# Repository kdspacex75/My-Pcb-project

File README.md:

# PCB Night-Vision Robot 🤖🔦

Custom Arduino UNO-compatible PCB design and robot prototype for obstacle detection with night vision.

## Features
- Designed PCB using **KiCad** and 3D modeled in **Fusion 360**
- Integrated night-vision sensors for obstacle detection
- Fully assembled robot hardware with Arduino-based control
- Hands-on electronics + robotics integration

## Tech Stack
- KiCad (PCB Design)
- Autodesk Fusion 360
- Arduino (C/C++)

---

### 🔗 Repository Info
This project was part of my robotics learning and showcases PCB design + embedded system integration.

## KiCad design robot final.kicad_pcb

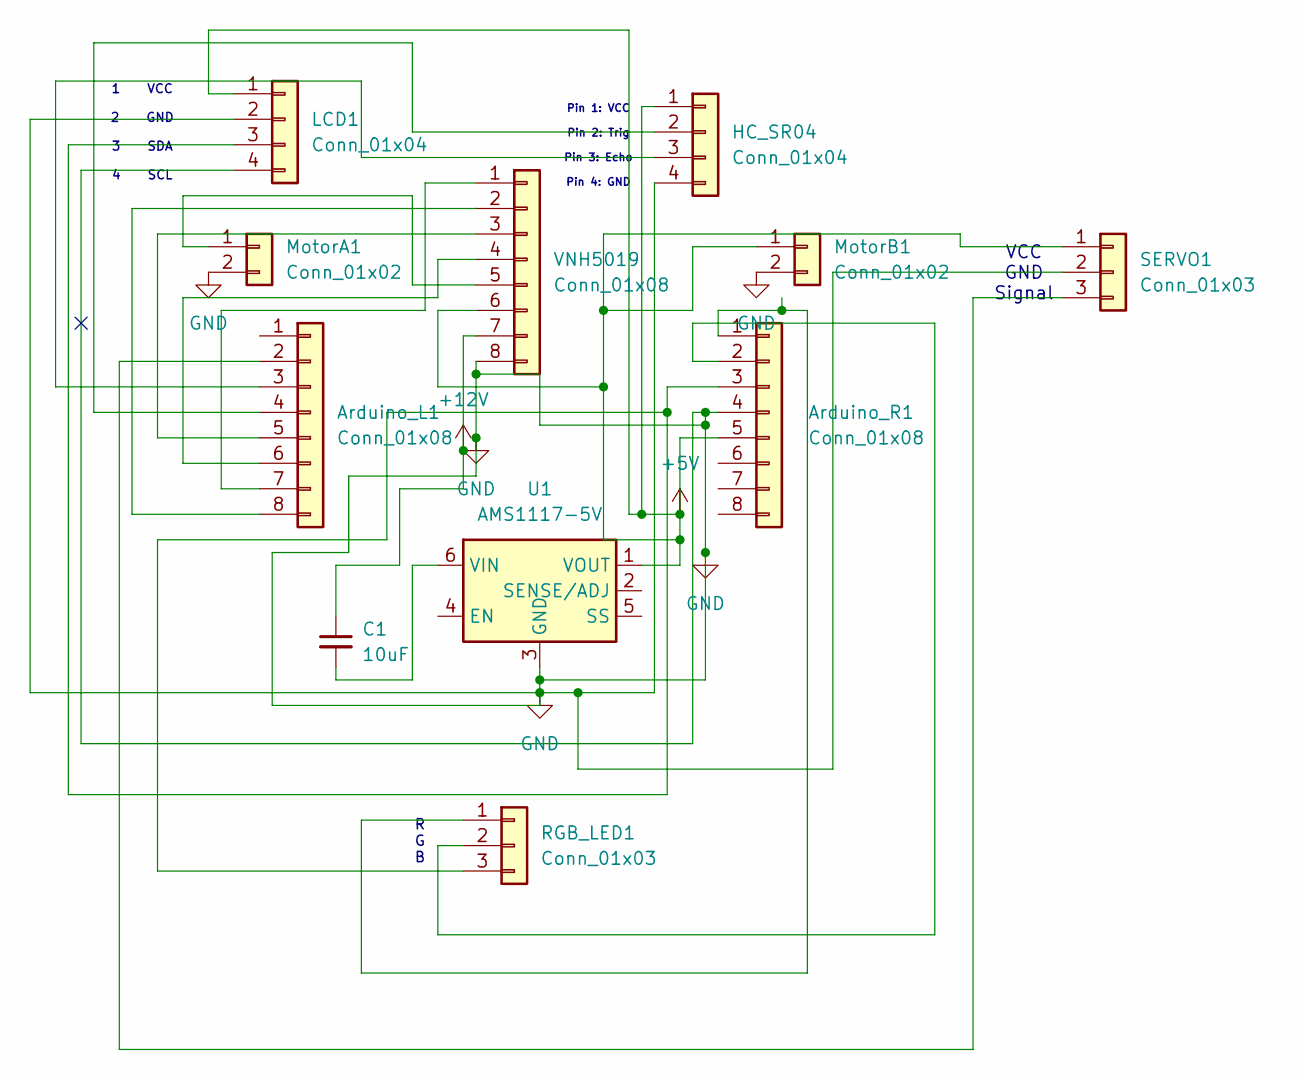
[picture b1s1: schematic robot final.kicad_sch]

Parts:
Arduino_L1: Conn_01x08; PinHeader_1x08_P2.54mm_Vertical
Arduino_R1: Conn_01x08; PinHeader_1x08_P2.54mm_Vertical
C1: 10uF; PinHeader_1x08_P2.54mm_Vertical
HC_SR04: Conn_01x04; PinHeader_1x04_P2.54mm_Vertical
LCD1: Conn_01x04; PinHeader_1x04_P2.54mm_Vertical
MotorA1: Conn_01x02; PinHeader_1x02_P2.54mm_Vertical
MotorB1: Conn_01x02; PinHeader_1x02_P2.54mm_Vertical
RGB_LED1: Conn_01x03; PinHeader_1x03_P2.54mm_Vertical
SERVO1: Conn_01x03; PinHeader_1x03_P2.54mm_Vertical
U1: AMS1117-5V; LFCSP-6-1EP_2x2mm_P0.65mm_EP1x1.6mm
VNH5019: Conn_01x08; PinHeader_1x08_P2.54mm_Vertical

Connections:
+5V: Arduino_R1.5, HC_SR04.1, LCD1.1, MotorB1.1, SERVO1.1, U1.1 (VOUT), VNH5019.6
+12V: C1.1, VNH5019.7
GND: Arduino_R1.4, HC_SR04.4, LCD1.2, LCD1.4, MotorA1.2, MotorB1.2, SERVO1.2, U1.3 (GND), U1.7 (GND), VNH5019.8
unnamed: Arduino_L1.2, SERVO1.3
unnamed: Arduino_L1.3, HC_SR04.3
unnamed: Arduino_L1.4, HC_SR04.2
unnamed: Arduino_L1.5, VNH5019.3
unnamed: Arduino_L1.6, VNH5019.4
unnamed: Arduino_L1.7, VNH5019.1
unnamed: Arduino_L1.8, VNH5019.2
unnamed: Arduino_R1.1, RGB_LED1.1
unnamed: Arduino_R1.2, RGB_LED1.2
unnamed: Arduino_R1.3, LCD1.3, RGB_LED1.3
unnamed: MotorA1.1, VNH5019.5
unnamed: C1.2, U1.6 (VIN)

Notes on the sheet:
VCC GND Signal
1 VCC 2 GND 3 SDA 4 SCL
R G B
Pin 1: VCC Pin 2: Trig Pin 3: Echo Pin 4: GND

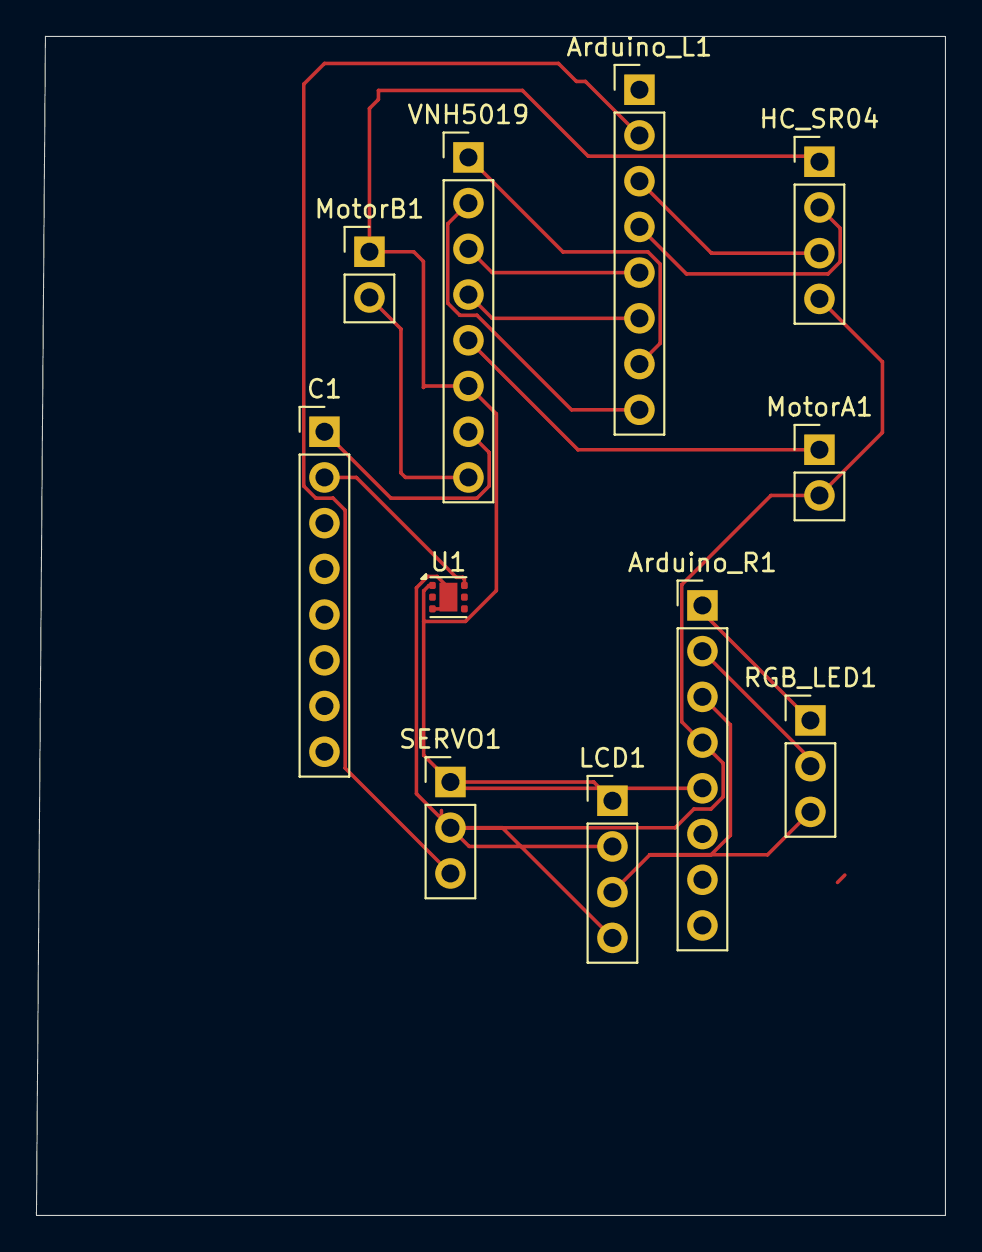
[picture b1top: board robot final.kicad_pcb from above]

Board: 2 copper layers, 50.5 x 65.5 mm, 11 parts (0 on the bottom side), 15 nets.
